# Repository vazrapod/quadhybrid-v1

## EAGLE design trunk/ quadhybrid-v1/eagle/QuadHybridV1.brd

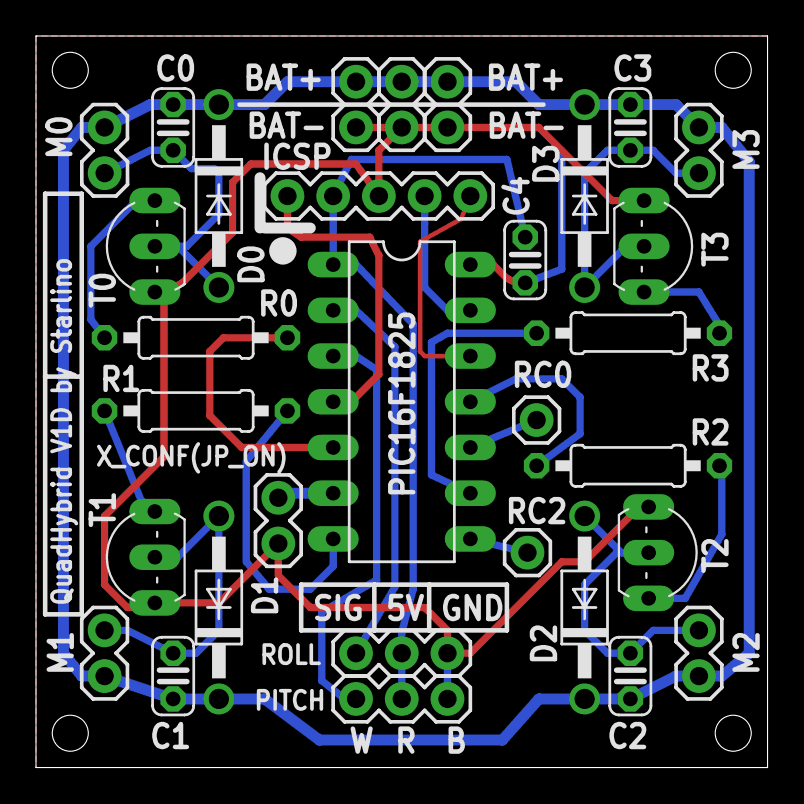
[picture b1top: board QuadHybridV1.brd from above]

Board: 2 copper layers, 40.6 x 40.6 mm, 31 parts (0 on the bottom side), 23 nets.

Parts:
C0, C1, C2, C3, C4: C025-024X044
D0, D1, D2, D3: 1N4004; DO41-10
ICSP: 1X05
JP1, JP2, JP3: 1X02
M0, M1, M2, M3: MOTOR; 1X02
PIC16F1825: PIC16F1825PDIP; DIL14
PITCH: 1X03
R0, R1, R2, R3: 510; 0207/10
RC0, RC2: M01PTH; 1X01
ROLL: 1X03
T0, T1, T2, T3: TO92-ECB
X_CONF(JP_ON): 1X02

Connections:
+5V: C4.1, ICSP.2, PIC16F1825.1, PITCH.2, ROLL.2
GND: C4.2, ICSP.3, JP1.2, JP2.2, JP3.2, PIC16F1825.14, PITCH.3, ROLL.3, T0.E, T1.E, T2.E, T3.E, X_CONF(JP_ON).2
unnamed: C0.2, D0.A, M0.2, T0.C
unnamed: C1.2, D1.A, M1.2, T1.C
unnamed: PIC16F1825.8, RC2.1
unnamed: PIC16F1825.6, X_CONF(JP_ON).1
unnamed: C2.2, D2.A, M2.2, T2.C
unnamed: PIC16F1825.10, RC0.1
unnamed: C3.2, D3.A, M3.2, T3.C
unnamed: R0.1, T0.B
unnamed: PIC16F1825.2, ROLL.1
unnamed: PIC16F1825.3, PITCH.1
unnamed: R1.1, T1.B
unnamed: R2.1, T2.B
unnamed: R3.1, T3.B
PGC: ICSP.5, PIC16F1825.12
PGD: ICSP.4, PIC16F1825.13
PWM0: PIC16F1825.5, R0.2
PWM1: PIC16F1825.7, R1.2
PWM2: PIC16F1825.11, R2.2
PWM3: PIC16F1825.9, R3.2
V+: C0.1, C1.1, C2.1, C3.1, D0.C, D1.C, D2.C, D3.C, JP1.1, JP2.1, JP3.1, M0.1, M1.1, M2.1, M3.1
VPP: ICSP.1, PIC16F1825.4

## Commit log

2012-12-01 Initial directory structure.
2016-02-04 Migrating wiki contents from Google Code

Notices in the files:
parts and their libraries:
SparkFun: Licensing: CC v3.0 Share-Alike You are welcome to use this library for commercial purposes.
